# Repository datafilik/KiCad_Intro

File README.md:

# KiCad_Intro

Contains the Schematic, PCB layout, and Gerber vector files for edit and production of a basic PCB board.
All files are the content of a KiCad project and can be edited  using KiCad.

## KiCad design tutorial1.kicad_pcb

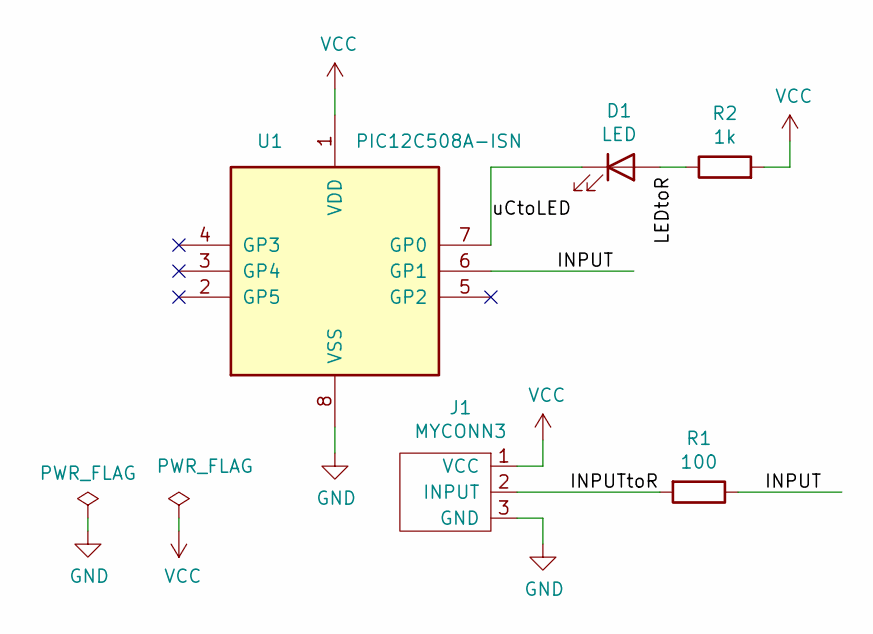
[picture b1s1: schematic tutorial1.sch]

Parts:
D1: LED; LED_D5.0mm
J1: MYCONN3; Banana_Jack_3Pin
R1: 100; R_Axial_DIN0207_L6.3mm_D2.5mm_P2.54mm_Vertical
R2: 1k; R_Axial_DIN0207_L6.3mm_D2.5mm_P2.54mm_Vertical
U1: PIC12C508A-ISN; DIP-8_W7.62mm

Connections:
/INPUT: R1.1, U1.6 (GP1)
/INPUTtoR: J1.2 (INPUT), R1.2
/uCtoLED: D1.1 (K), U1.7 (GP0)
GND: J1.3 (GND), U1.8 (VSS)
unnamed: D1.2 (A), R2.1
VCC: J1.1 (VCC), R2.2, U1.1 (VDD)

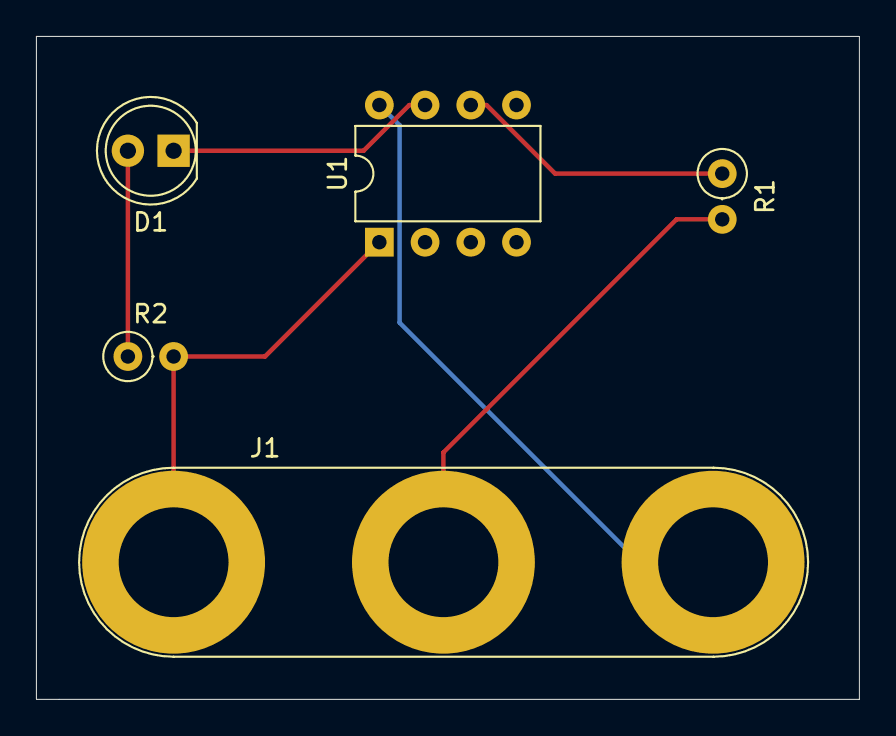
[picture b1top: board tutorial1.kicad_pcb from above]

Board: 2 copper layers, 45.7 x 36.8 mm, 5 parts (0 on the bottom side), 6 nets.
